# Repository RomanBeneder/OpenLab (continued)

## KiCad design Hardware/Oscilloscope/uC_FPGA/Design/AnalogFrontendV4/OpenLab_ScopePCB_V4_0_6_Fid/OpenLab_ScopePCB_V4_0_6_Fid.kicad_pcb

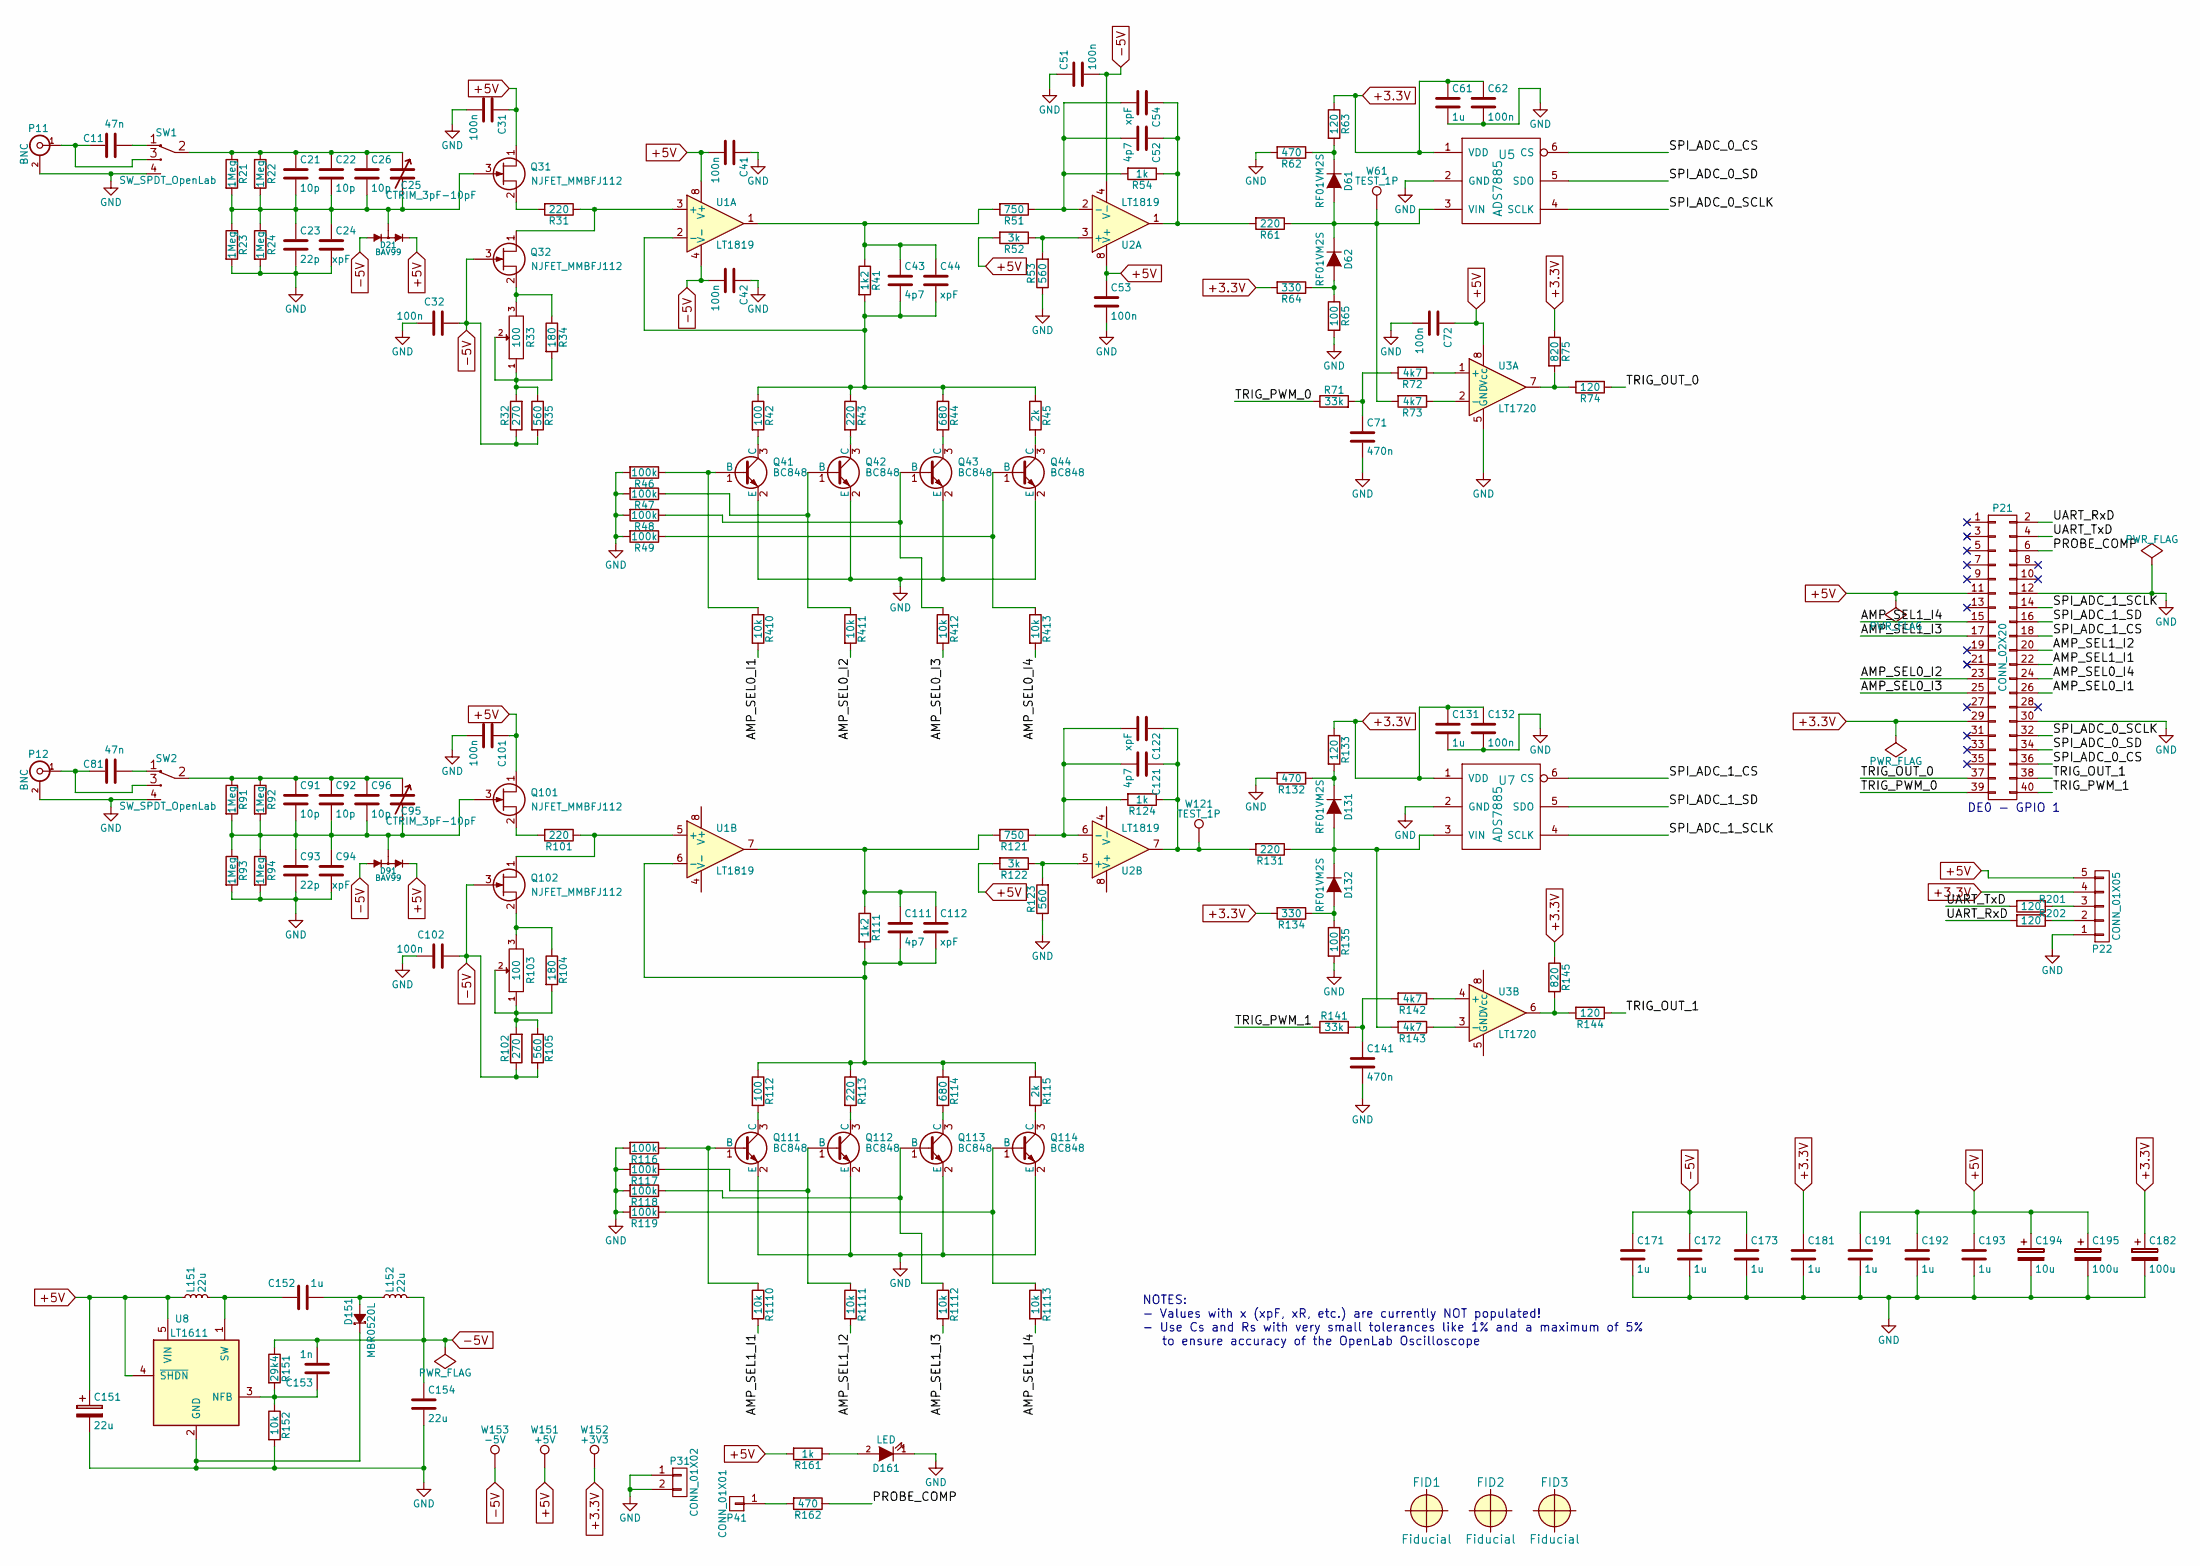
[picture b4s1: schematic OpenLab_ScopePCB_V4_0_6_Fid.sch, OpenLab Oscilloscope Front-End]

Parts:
C11, C81: 47n; C_0603_HandSoldering
C21, C22, C26, C91, C92, C96: 10p; C_0603_HandSoldering
C23, C93: 22p; C_0603_HandSoldering
C24, C44, C54, C94, C112, C122: xpF; C_0603_HandSoldering
C25, C95: CTRIM_3pF-10pF; TRIM_CO
C31, C32, C41, C42, C51, C53, C62, C72, C101, C102, C132: 100n; C_0603_HandSoldering
C43, C52, C111, C121: 4p7; C_0603_HandSoldering
C61, C131, C152, C171, C172, C173, C181, C191, C192, C193: 1u; C_0603_HandSoldering
C71, C141: 470n; C_0603_HandSoldering
C151: 22u; C_1206_HandSoldering
C153: 1n; C_0603_HandSoldering
C154: 22u; C_1210_HandSoldering
C182, C195: 100u; c_elec_6.3x5.8
C194: 10u; c_elec_5x5.3
D21, D91: BAV99; SOT-23
D61, D62, D131, D132: RF01VM2S; SOD-323_RF01VM_DIODE
D151: MBR0520L; D_SOD-123
D161: LED; LED-0805
FID1, FID2, FID3: Fiducial; Fiducial_1.5mm_Dia_2.54mm_Outer_CopperTop
L151, L152: 22u; Choke_SMD_Bourns_SRN4026
P11, P12: BNC; BNC_Socket_TYCO-AMP
P21: CONN_02X20; Pin_Header_Straight_2x20_Pitch2.54mm_OPENLAB
P22: CONN_01X05; Pin_Header_Straight_1x05_Pitch2.54mm
P31: CONN_01X02; Pin_Header_Straight_2x01_Pitch2.54mm
P41: CONN_01X01; Pin_Header_Straight_1x01_Pitch2.54mm
Q31, Q32, Q101, Q102: NJFET_MMBFJ112; SOT-23
Q41, Q42, Q43, Q44, Q111, Q112, Q113, Q114: BC848; SOT-23
R21, R22, R23, R24, R91, R92, R93, R94: 1Meg; R_0603_HandSoldering
R31, R43, R61, R101, R113, R131: 220; R_0603_HandSoldering
R32, R102: 270; R_0603_HandSoldering
R33, R103: 100; Potentiometer_SMD_OpenLab
R34, R104: 180; R_0603_HandSoldering
R35, R53, R105, R123: 560; R_0603_HandSoldering
R41, R111: 1k2; R_0603_HandSoldering
R42, R65, R112, R135: 100; R_0603_HandSoldering
R44, R114: 680; R_0603_HandSoldering
R45, R115: 2k; R_0603_HandSoldering
R46, R47, R48, R49, R116, R117, R118, R119: 100k; R_0603_HandSoldering
R51, R121: 750; R_0603_HandSoldering
R52, R122: 3k; R_0603_HandSoldering
R54, R124, R161: 1k; R_0603_HandSoldering
R62, R132, R162: 470; R_0603_HandSoldering
R63, R74, R133, R144, R201, R202: 120; R_0603_HandSoldering
R64, R134: 330; R_0603_HandSoldering
R71, R141: 33k; R_0603_HandSoldering
R72, R73, R142, R143: 4k7; R_0603_HandSoldering
R75, R145: 820; R_0603_HandSoldering
R151: 29k4; R_0603_HandSoldering
R152, R410, R411, R412, R413, R1110, R1111, R1112, R1113: 10k; R_0603_HandSoldering
SW1, SW2: SW_SPDT_OpenLab; SWITCH-2-WAY_SPDT
U1, U2: LT1819; SOIC-8_3_LT1819
U3: LT1720; SOIC-8_3_LT1819
U5, U7: ADS7885; TSOT-6_ADS7885
U8: LT1611; sot23-5_LT1611
W61, W121: TEST_1P; Test_Pad
W151: +5V; Test_Pad
W152: +3V3; Test_Pad
W153: -5V; Test_Pad

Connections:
+3.3V: C61.1, C62.1, C131.1, C132.1, C181.1, C182.1, P21.29, P22.4, R63.1, R64.2, R75.1, R133.1, R134.2, R145.1, U5.1 (VDD), U7.1 (VDD), W152.1
+5V: C31.1, C41.2, C53.1, C72.1, C101.1, C151.1, C191.1, C192.1, C193.1, C194.1, C195.1, D21.2 (K), D91.2 (K), L151.1, P21.11, P22.5, Q31.1 (D), Q101.1 (D), R52.2, R122.2, R161.2, U1.8 (V+), U2.8 (V+), U3.8 (Vcc), U8.4 (~SHDN~), U8.5 (VIN), W151.1
-5V: C32.2, C42.2, C51.2, C102.2, C153.2, C154.1, C171.1, C172.1, C173.1, D21.1 (A), D91.1 (A), L152.2, Q32.3 (G), Q102.3 (G), R32.1, R35.2, R102.1, R105.2, R151.1, U1.4 (V-), U2.4 (V-), W153.1
/AMP_SEL0_I1: P21.26, R410.2
/AMP_SEL0_I2: P21.23, R411.2
/AMP_SEL0_I3: P21.25, R412.2
/AMP_SEL0_I4: P21.24, R413.2
/AMP_SEL1_I1: P21.22, R1110.2
/AMP_SEL1_I2: P21.20, R1111.2
/AMP_SEL1_I3: P21.17, R1112.2
/AMP_SEL1_I4: P21.15, R1113.2
/PROBE_COMP: P21.6, R162.1
/SPI_ADC_0_CS: P21.36, U5.6 (CS)
/SPI_ADC_0_SCLK: P21.32, U5.4 (SCLK)
/SPI_ADC_0_SD: P21.34, U5.5 (SDO)
/SPI_ADC_1_CS: P21.18, U7.6 (CS)
/SPI_ADC_1_SCLK: P21.14, U7.4 (SCLK)
/SPI_ADC_1_SD: P21.16, U7.5 (SDO)
/TRIG_OUT_0: P21.37, R74.1
/TRIG_OUT_1: P21.38, R144.1
/TRIG_PWM_0: P21.39, R71.1
/TRIG_PWM_1: P21.40, R141.1
/UART_RxD: P21.2, R202.2
/UART_TxD: P21.4, R201.2
GND: C23.2, C24.2, C31.2, C32.1, C41.1, C42.1, C51.1, C53.2, C61.2, C62.2, C71.2, C72.2, C93.2, C94.2, C101.2, C102.1, C131.2, C132.2, C141.2, C151.2, C154.2, C171.2, C172.2, C173.2, C181.2, C182.2, C191.2, C192.2, C193.2, C194.2, C195.2, D151.1 (K), D161.1 (K), P11.2 (Ext), P12.2 (Ext), P21.12, P21.30, P22.1, P31.1, P31.2, Q41.2 (E), Q42.2 (E), Q43.2 (E), Q44.2 (E), Q111.2 (E), Q112.2 (E), Q113.2 (E), Q114.2 (E), R23.2, R24.2, R46.2, R47.2, R48.2, R49.2, R53.1, R62.2, R65.2, R93.2, R94.2, R116.2, R117.2, R118.2, R119.2, R123.1, R132.2, R135.2, R152.2, SW1.4 (FRAME), SW2.4 (FRAME), U3.5 (GND), U5.2 (GND), U7.2 (GND), U8.2 (GND)
unnamed: C11.1, SW1.1 (AC)
unnamed: C11.2, P11.1 (In), SW1.3 (DC)
unnamed: C21.1, C22.1, C25.1, C26.1, R21.1, R22.1, SW1.2 (SIG)
unnamed: C21.2, C22.2, C23.1, C24.1, C25.2, C26.2, D21.3 (KA), Q31.3 (G), R21.2, R22.2, R23.1, R24.1
unnamed: C43.1, C44.1, R41.1, R51.2, U1.1
unnamed: C43.2, C44.2, R41.2, R42.1, R43.1, R44.1, R45.1, U1.2 (-)
unnamed: C52.1, C54.1, R54.1, R61.2, U2.1
unnamed: C52.2, C54.2, R51.1, R54.2, U2.2 (-)
unnamed: C71.1, R71.2, R72.2
unnamed: C81.1, SW2.1 (AC)
unnamed: C81.2, P12.1 (In), SW2.3 (DC)
unnamed: C91.1, C92.1, C95.1, C96.1, R91.1, R92.1, SW2.2 (SIG)
unnamed: C91.2, C92.2, C93.1, C94.1, C95.2, C96.2, D91.3 (KA), Q101.3 (G), R91.2, R92.2, R93.1, R94.1
unnamed: C111.1, C112.1, R111.1, R121.2, U1.7
unnamed: C111.2, C112.2, R111.2, R112.1, R113.1, R114.1, R115.1, U1.6 (-)
unnamed: C121.1, C122.1, R124.1, R131.2, U2.7, W121.1
unnamed: C121.2, C122.2, R121.1, R124.2, U2.6 (-)
unnamed: C141.1, R141.2, R142.2
unnamed: C152.1, L151.2, U8.1 (SW)
unnamed: C152.2, D151.2 (A), L152.1
unnamed: C153.1, R151.2, R152.1, U8.3 (NFB)
unnamed: D61.1 (K), R62.1, R63.2
unnamed: D61.2 (A), D62.1 (K), R61.1, R73.2, U5.3 (VIN), W61.1
unnamed: D62.2 (A), R64.1, R65.1
unnamed: D131.1 (K), R132.1, R133.2
unnamed: D131.2 (A), D132.1 (K), R131.1, R143.2, U7.3 (VIN)
unnamed: D132.2 (A), R134.1, R135.1
unnamed: D161.2 (A), R161.1
unnamed: P22.2, R202.1
unnamed: P22.3, R201.1
unnamed: P41.1, R162.2
unnamed: Q31.2 (S), R31.2
unnamed: Q32.1 (D), R31.1, U1.3 (+)
unnamed: Q32.2 (S), R33.3, R34.1
unnamed: Q41.1 (B), R46.1, R410.1
unnamed: Q41.3 (C), R42.2
unnamed: Q42.1 (B), R47.1, R411.1
unnamed: Q42.3 (C), R43.2
unnamed: Q43.1 (B), R48.1, R412.1
unnamed: Q43.3 (C), R44.2
unnamed: Q44.1 (B), R49.1, R413.1
unnamed: Q44.3 (C), R45.2
unnamed: Q101.2 (S), R101.2
unnamed: Q102.1 (D), R101.1, U1.5 (+)
unnamed: Q102.2 (S), R103.3, R104.1
unnamed: Q111.1 (B), R116.1, R1110.1
unnamed: Q111.3 (C), R112.2
unnamed: Q112.1 (B), R117.1, R1111.1
unnamed: Q112.3 (C), R113.2
unnamed: Q113.1 (B), R118.1, R1112.1
unnamed: Q113.3 (C), R114.2
unnamed: Q114.1 (B), R119.1, R1113.1
unnamed: Q114.3 (C), R115.2
unnamed: R32.2, R33.1, R33.2, R34.2, R35.1
unnamed: R52.1, R53.2, U2.3 (+)
unnamed: R72.1, U3.1 (+)
unnamed: R73.1, U3.2 (-)
unnamed: R74.2, R75.2, U3.7
unnamed: R102.2, R103.1, R103.2, R104.2, R105.1
unnamed: R122.1, R123.2, U2.5 (+)
unnamed: R142.1, U3.4 (+)
unnamed: R143.1, U3.3 (-)
unnamed: R144.2, R145.2, U3.6

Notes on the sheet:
DE0 - GPIO 1
NOTES: - Values with x (xpF, xR, etc.) are currently NOT populated! - Use Cs and Rs with very small tolerances like 1% and a maximum of 5% to ensure accuracy of the OpenLab Oscilloscope

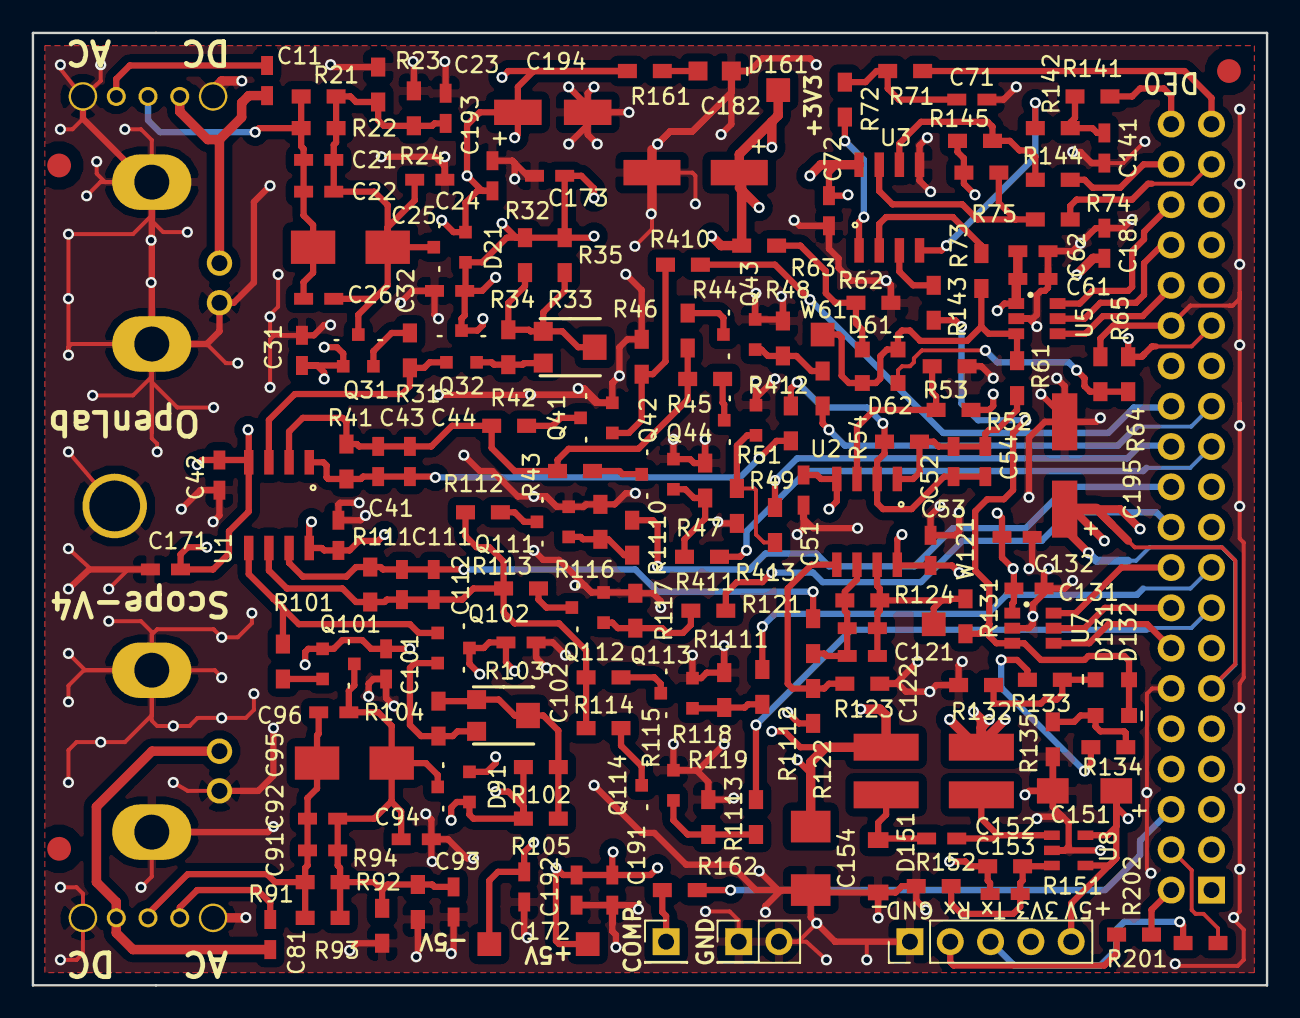
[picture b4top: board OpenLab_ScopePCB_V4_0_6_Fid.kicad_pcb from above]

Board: 4 copper layers, 77.8 x 60.0 mm, 173 parts (0 on the bottom side), 88 nets.

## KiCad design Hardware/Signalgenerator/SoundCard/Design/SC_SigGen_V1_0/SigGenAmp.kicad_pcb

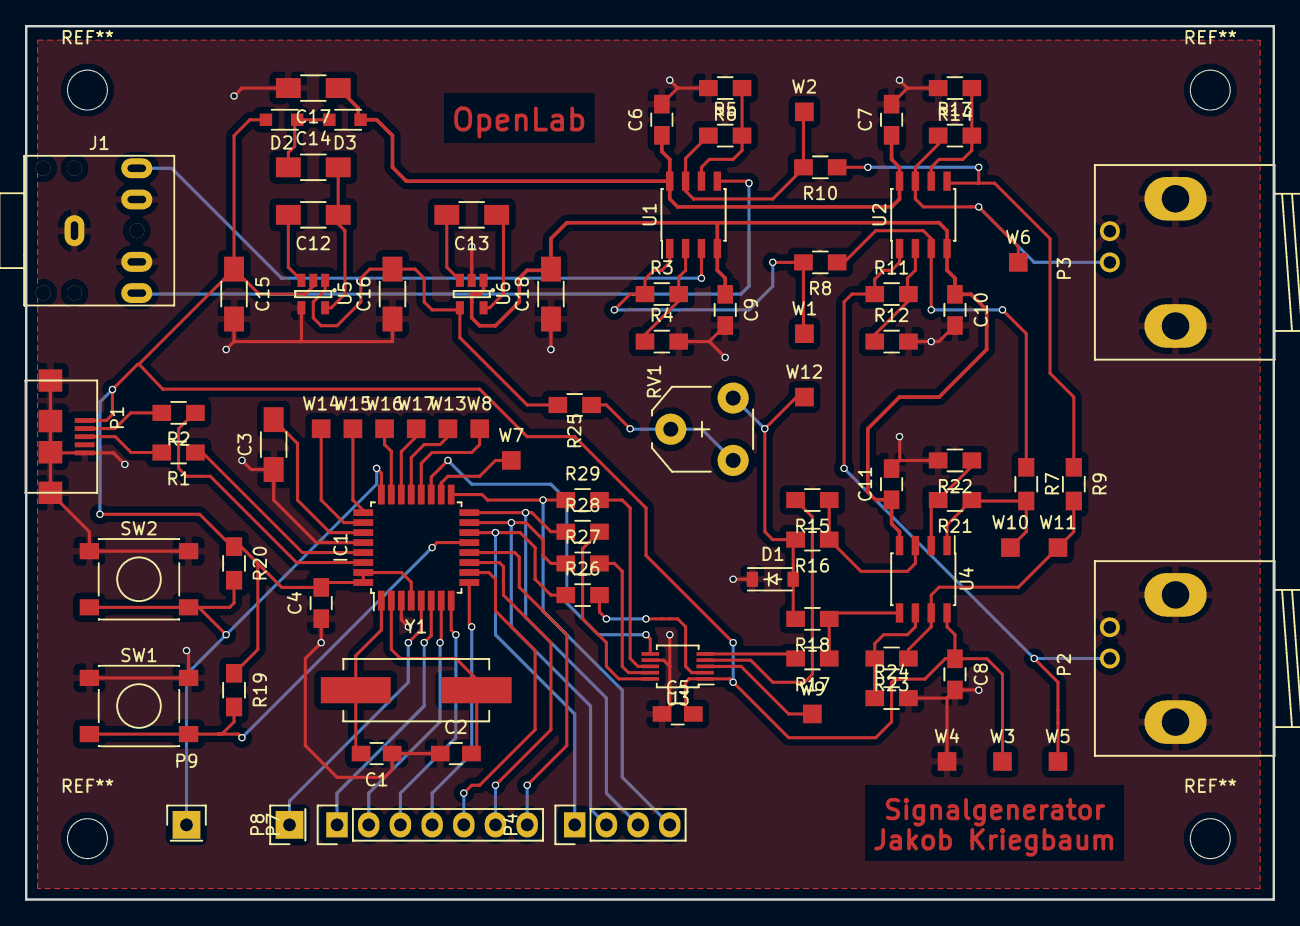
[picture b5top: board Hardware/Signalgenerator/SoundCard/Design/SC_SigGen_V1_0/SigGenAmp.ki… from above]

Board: 2 copper layers, 100.0 x 70.0 mm, 86 parts (0 on the bottom side), 66 nets.

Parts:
C1, C2: 22pF; C_0805_HandSoldering
C3, C12, C13, C14, C15, C16, C17, C18: 1uF; C_1206_HandSoldering
C4: 100nF; C_0805_HandSoldering
C5, C6, C7, C8, C9, C10, C11: 100n; C_0805_HandSoldering
D1: 2.5V; SOD-123
D2, D3: D; SOD-323_HandSoldering
IC1: ATMEGA8U2; TQFP-32_7x7mm_Pitch0.8mm
J1: JACK_TRS_6PINS; TRS 3.5mm 5PIN
P1: USB_OTG; USB_Micro-B_SMD
P2: CH1; BNC_Socket_TYCO-AMP_FIX
P3: CH2; BNC_Socket_TYCO-AMP_FIX
P4: SPI; Pin_Header_Straight_1x04
P7: PORTD; Pin_Header_Straight_1x07
P8: PC; Pin_Header_Straight_1x01
P9: dW; Pin_Header_Straight_1x01
R1, R2: 22; R_0805_HandSoldering
R3, R5: 110k; R_0805_HandSoldering
R4, R6, R11, R12, R13, R14, R19, R20, R22, R24: 10k; R_0805_HandSoldering
R7, R8, R9, R10, R15, R16, R17, R18: 100k; R_0805_HandSoldering
R21, R23: 30k; R_0805_HandSoldering
R25: 1k; R_0805_HandSoldering
R26, R27, R28, R29: 100; R_0805_HandSoldering
RV1: 2k5; Potentiometer_VishaySpectrol-Econtrim-Type36M
SW1, SW2: SW_PUSH; SW_SPST_PTS645
U1, U2: AD8034; SOIC-8_3.9x4.9mm_Pitch1.27mm
U3: MCP48FEB02; MSOP-10_3x3mm_Pitch0.5mm
U4: MC33202; SOIC-8_3.9x4.9mm_Pitch1.27mm
U5, U6: TPS60400DBVR; SOT-23-5
W1: AMP1; Measurement_Point_Square-SMD-Pad_Small
W2: AMP2; Measurement_Point_Square-SMD-Pad_Small
W3: VCC; Measurement_Point_Square-SMD-Pad_Small
W4: GND; Measurement_Point_Square-SMD-Pad_Small
W5: SIG1; Measurement_Point_Square-SMD-Pad_Small
W6: SIG2; Measurement_Point_Square-SMD-Pad_Small
W7: PB4; Measurement_Point_Square-SMD-Pad_Small
W8: PB6; Measurement_Point_Square-SMD-Pad_Small
W9: DACREF; Measurement_Point_Square-SMD-Pad_Small
W10: OFF1; Measurement_Point_Square-SMD-Pad_Small
W11: OFF2; Measurement_Point_Square-SMD-Pad_Small
W12: REF; Measurement_Point_Square-SMD-Pad_Small
W13, W14, W15, W16, W17: PB7; Measurement_Point_Square-SMD-Pad_Small
Y1: 16MHz; Crystal_HC49-SD_SMD

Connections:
GND: C1.1, C2.1, C3.1, C4.1, C5.1, C6.2, C7.2, C8.2, C9.2, C10.2, C11.2, C15.2, C16.1, C17.2, C18.1, D1.1, IC1.3, IC1.28, J1.1, J1.5, J1.6, P1.5, P1.6, P2.2, P3.2, R4.2, R6.2, R12.2, R14.2, R22.2, R24.2, SW1.1, SW2.1, U3.7, U5.4, U6.2, W4.1
HWB: IC1.13, R19.2, SW1.2
unnamed: C1.2, IC1.1, Y1.1
unnamed: C2.2, IC1.2, Y1.2
unnamed: C3.2, IC1.27
unnamed: C12.1, C14.2, U5.5
unnamed: C12.2, U5.3
unnamed: C13.1, U6.5
unnamed: C13.2, U6.3
unnamed: C14.1, D2.1, D3.2
unnamed: IC1.5, P8.1
unnamed: IC1.6, P7.1
unnamed: IC1.7, P7.2
unnamed: IC1.8, P7.3
unnamed: IC1.9, P7.4
unnamed: IC1.10, P7.5
unnamed: IC1.11, P7.6
unnamed: IC1.12, P7.7
unnamed: IC1.14, P4.1, R26.1
unnamed: IC1.15, P4.2, R27.1
unnamed: IC1.16, P4.3, R28.1
unnamed: IC1.17, P4.4, R29.1
unnamed: IC1.18, W7.1
unnamed: IC1.19, U3.6
unnamed: IC1.20, W8.1
unnamed: IC1.21, W13.1
unnamed: IC1.22, W17.1
unnamed: IC1.23, W16.1
unnamed: IC1.25, W15.1
unnamed: IC1.26, W14.1
unnamed: IC1.29, R1.1
unnamed: IC1.30, R2.1
unnamed: J1.2, U1.3
unnamed: J1.3, U1.5
unnamed: P1.2, R2.2
unnamed: P1.3, R1.2
unnamed: P2.1, R11.1, U2.1, W5.1
unnamed: P3.1, R13.1, U2.7, W6.1
unnamed: R3.1, R8.2, U1.1, W1.1
unnamed: R3.2, R4.1, U1.2
unnamed: R5.2, R6.1, U1.6
unnamed: R7.1, R8.1, U2.3
unnamed: R9.1, R10.1, U2.5
unnamed: R5.1, R10.2, U1.7, W2.1
unnamed: R11.2, R12.1, U2.2
unnamed: R13.2, R14.1, U2.6
unnamed: R15.1, R16.1, U4.3
unnamed: R17.1, R18.1, U4.5
unnamed: R21.2, R22.1, U4.2
unnamed: R23.2, R24.1, U4.6
unnamed: R25.1, RV1.1, RV1.2
unnamed: R26.2, U3.2
unnamed: R27.2, U3.9
unnamed: R28.2, U3.10
unnamed: R29.2, U3.8
unnamed: U3.3, W9.1
Offset1: R7.2, R21.1, U4.1, W10.1
Offset2: R9.2, R23.1, U4.7, W11.1
RESET: IC1.24, P9.1, R20.2, SW2.2
RawOffset1: R15.2, U3.4
RawOffset2: R17.2, U3.5
V+: C6.1, C7.1, C17.1, D3.1, U1.8, U2.8
V-: C9.1, C10.1, C11.1, C18.2, U1.4, U2.4, U4.4, U6.1
VCC: C4.2, C5.2, C8.1, C15.1, D2.2, IC1.4, IC1.31, IC1.32, P1.1, R19.1, R20.1, U3.1, U4.8, U5.2, W3.1
VRef-: D1.2, R16.2, R18.2, RV1.3, W12.1
VSS: C16.2, R25.2, U5.1, U6.4

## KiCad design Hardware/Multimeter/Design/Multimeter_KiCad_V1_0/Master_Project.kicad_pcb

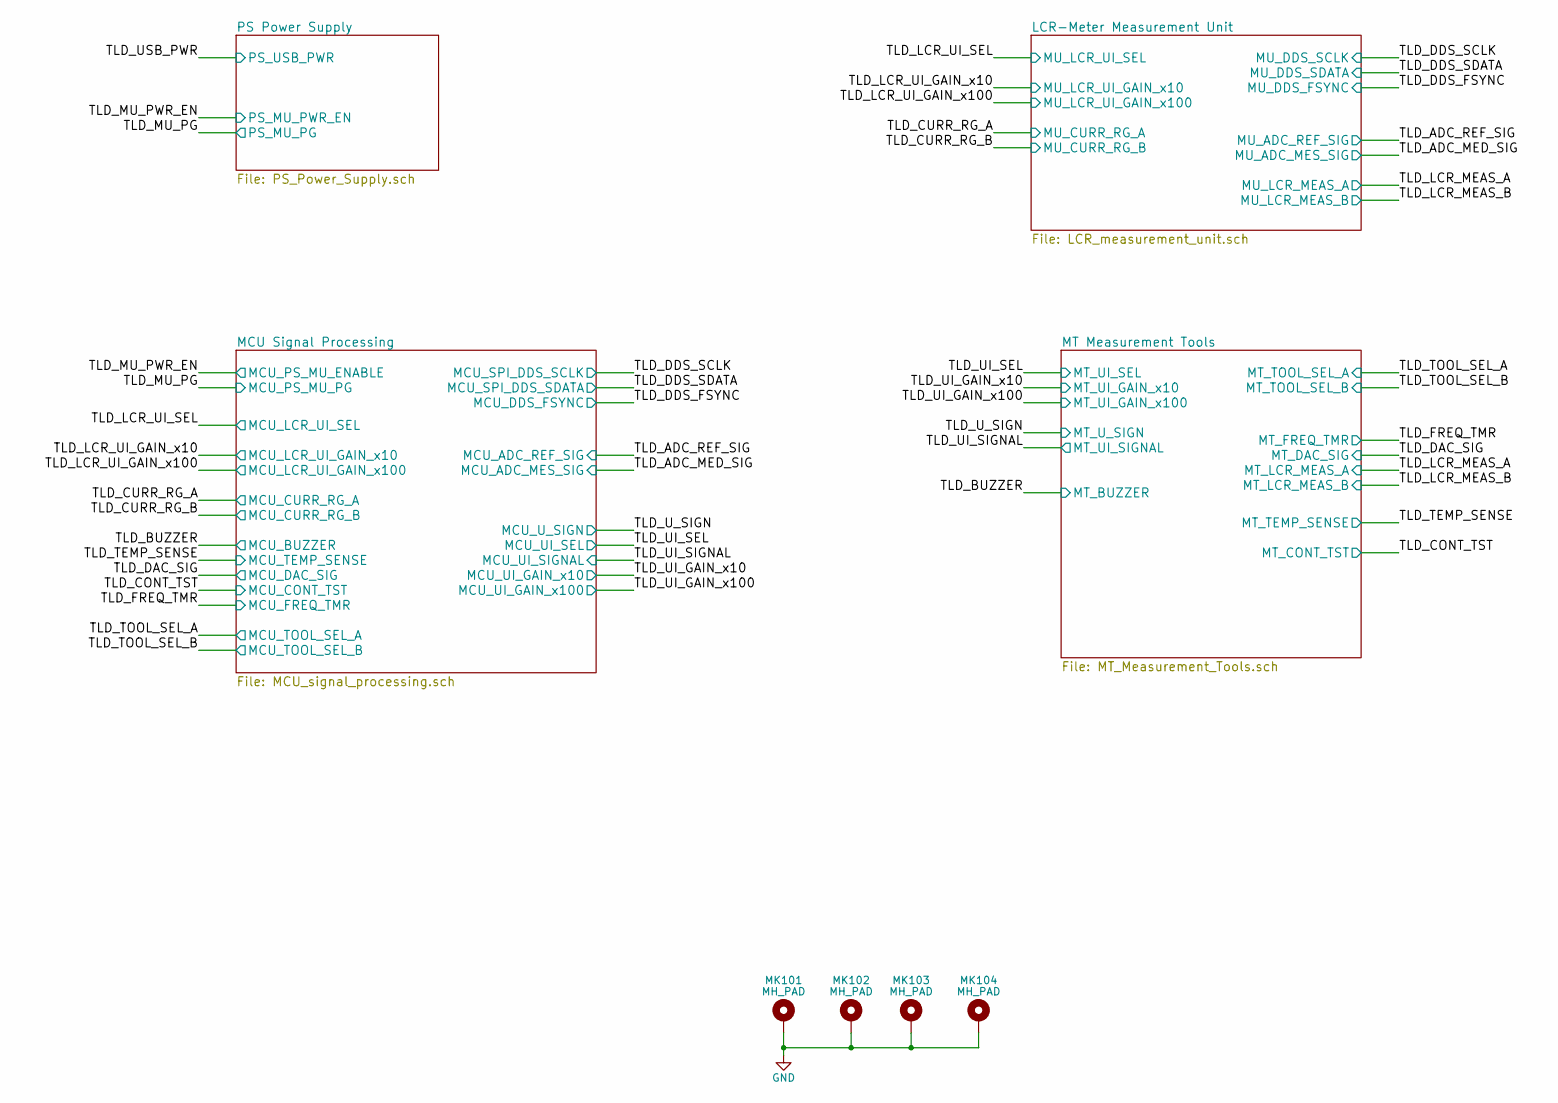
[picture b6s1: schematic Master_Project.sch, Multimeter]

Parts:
MK101, MK102, MK103, MK104: MH_PAD; MountingHole_3.2mm_M3_DIN965_Pad

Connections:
GND: MK101.1, MK102.1, MK103.1, MK104.1; also elsewhere on the board

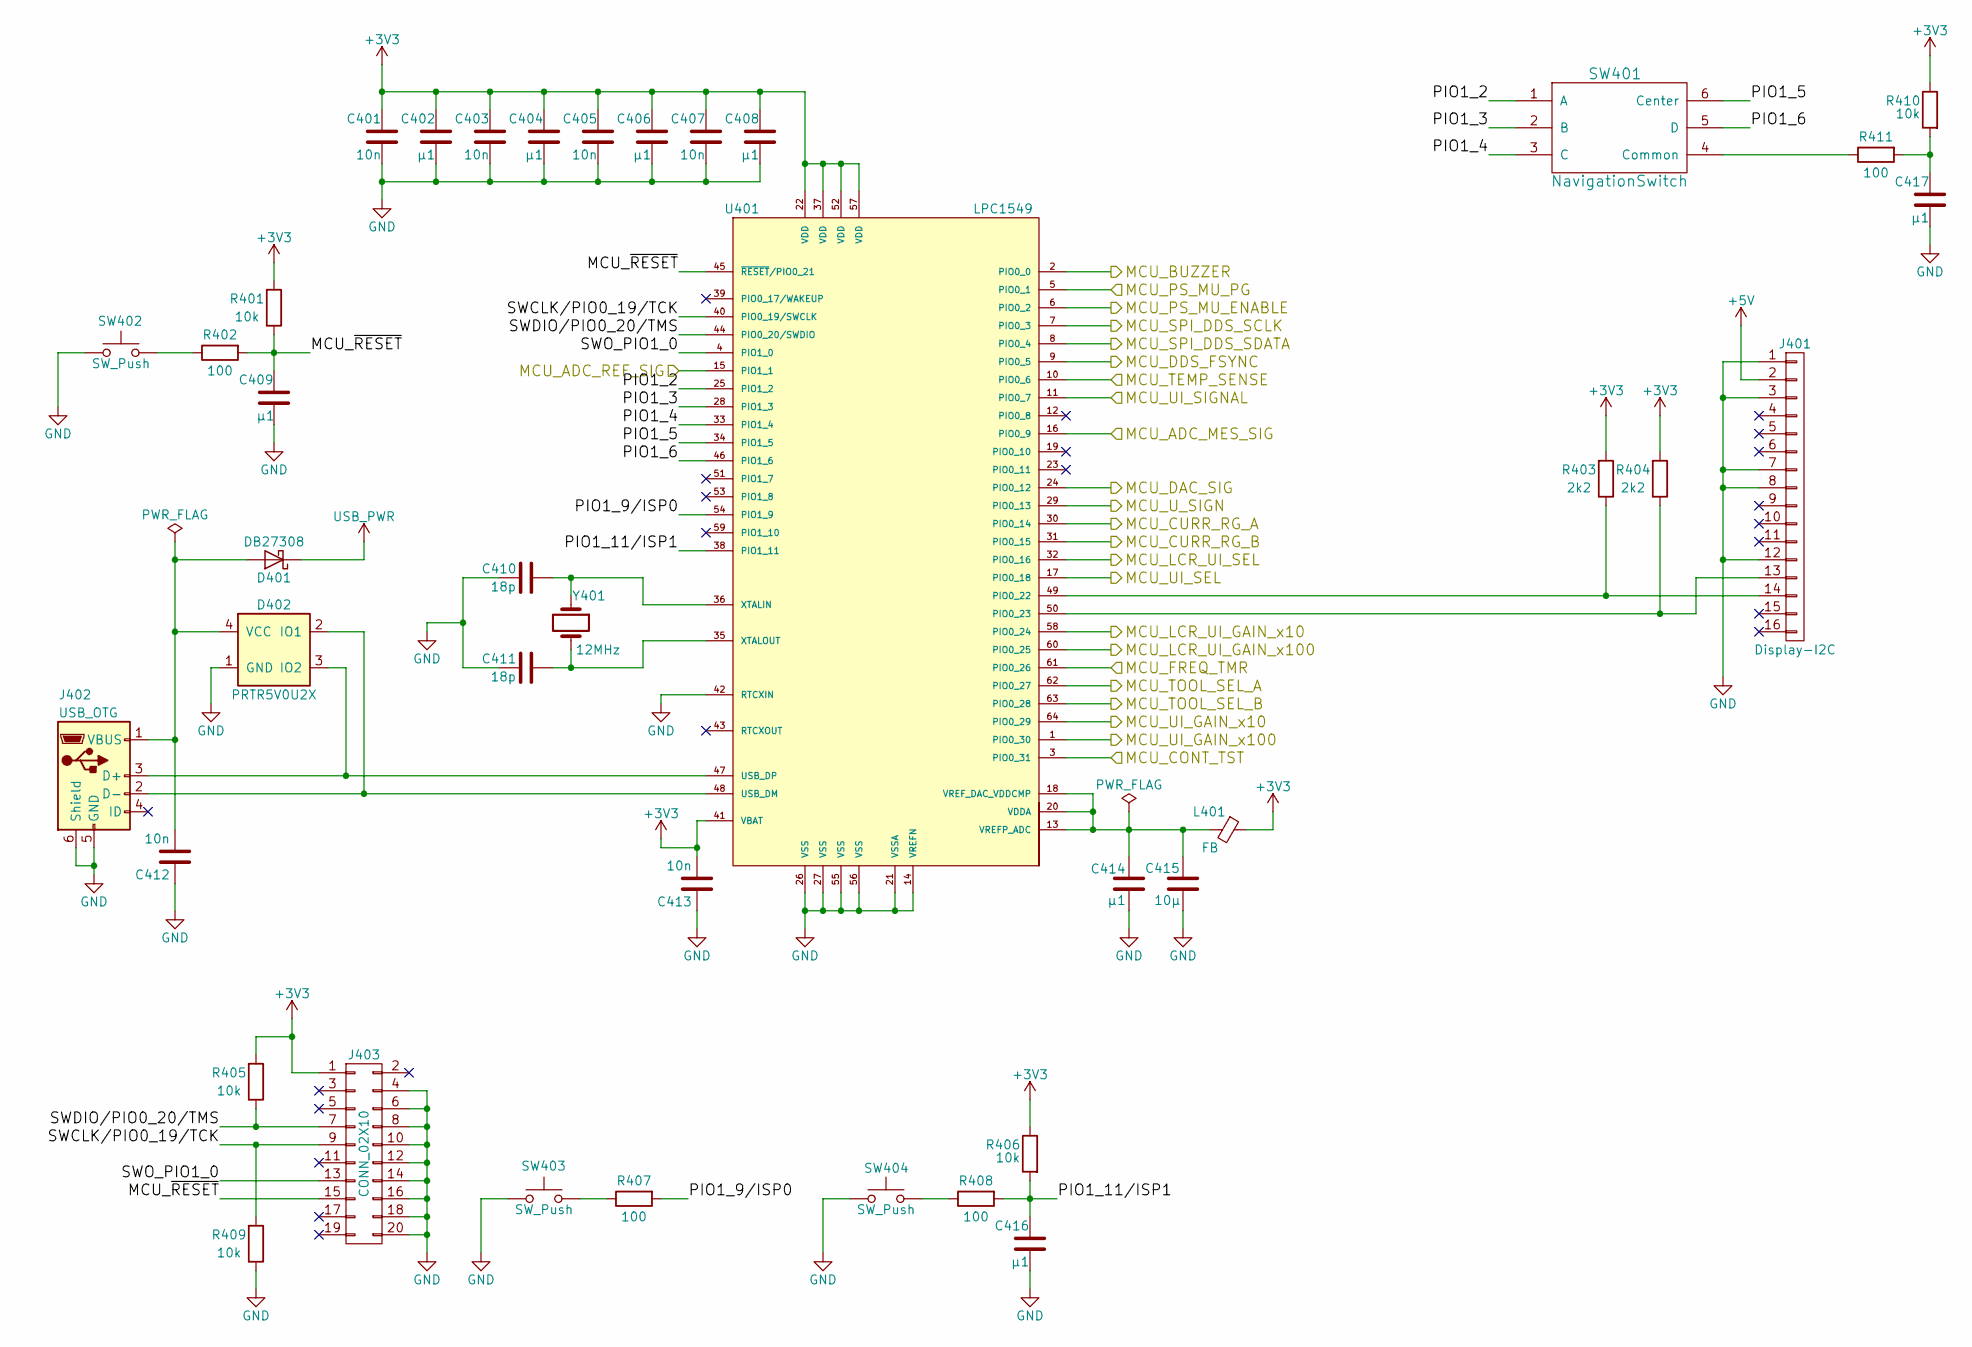
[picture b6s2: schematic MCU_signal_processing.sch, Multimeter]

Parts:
C401, C403, C405, C407, C412, C413: 10n; C_0603
C402, C404, C406, C408, C409, C414, C416, C417: µ1; C_0603
C410, C411: 18p; C_0603
C415: 10µ; C_1206
D401: DB27308; D_0603
D402: PRTR5V0U2X; SOT-143
J401: Display-I2C; Pin_Header_Straight_1x16_Pitch2.54mm
J402: USB_OTG; USB_Micro_B
J403: CONN_02X10; Pin_Header_Straight_2x10_Pitch2.54mm
L401: FB; R_0805
R401, R405, R406, R409, R410: 10k; R_0603
R402, R407, R408, R411: 100; R_0603
R403, R404: 2k2; R_0603
SW401: NavigationSwitch; SKQUCAA010_SKQU_5_Polig_ALPS
SW402, SW403, SW404: SW_Push; SW_SPST_KMR2
U401: LPC1549; LQFP-64_10x10mm_Pitch0.5mm
Y401: 12MHz; Crystal_SMD_0603-2pin_6.0x3.5mm

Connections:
+3V3: C401.2, C402.2, C403.2, C404.2, C405.2, C406.2, C407.2, C408.2, C413.2, J403.1, L401.1, R401.2, R403.2, R404.2, R405.2, R406.1, R410.1, U401.22 (VDD), U401.37 (VDD), U401.41 (VBAT), U401.52 (VDD), U401.57 (VDD); also elsewhere on the board
+5V: J401.2; also elsewhere on the board
/MCU Signal Processing/MCU_~RESET~: C409.2, J403.15, R401.1, R402.2, U401.45 (~RESET~/PIO0_21)
/MCU Signal Processing/PIO1_2: SW401.1 (A), U401.25 (PIO1_2)
/MCU Signal Processing/PIO1_3: SW401.2 (B), U401.28 (PIO1_3)
/MCU Signal Processing/PIO1_4: SW401.3 (C), U401.33 (PIO1_4)
/MCU Signal Processing/PIO1_5: SW401.6 (Center), U401.34 (PIO1_5)
/MCU Signal Processing/PIO1_6: SW401.5 (D), U401.46 (PIO1_6)
/MCU Signal Processing/PIO1_9/ISP0: R407.2, U401.54 (PIO1_9)
/MCU Signal Processing/PIO1_11/ISP1: C416.2, R406.2, R408.2, U401.38 (PIO1_11)
/MCU Signal Processing/SWCLK/PIO0_19/TCK: J403.9, R409.2, U401.40 (PIO0_19/SWCLK)
/MCU Signal Processing/SWDIO/PIO0_20/TMS: J403.7, R405.1, U401.44 (PIO0_20/SWDIO)
/MCU Signal Processing/SWO_PIO1_0: J403.13, U401.4 (PIO1_0)
/TLD_ADC_MED_SIG: U401.16 (PIO0_9); also elsewhere on the board
/TLD_ADC_REF_SIG: U401.15 (PIO1_1); also elsewhere on the board
/TLD_BUZZER: U401.2 (PIO0_0); also elsewhere on the board
/TLD_CONT_TST: U401.3 (PIO0_31); also elsewhere on the board
/TLD_CURR_RG_A: U401.30 (PIO0_14); also elsewhere on the board
/TLD_CURR_RG_B: U401.31 (PIO0_15); also elsewhere on the board
/TLD_DAC_SIG: U401.24 (PIO0_12); also elsewhere on the board
/TLD_DDS_FSYNC: U401.9 (PIO0_5); also elsewhere on the board
/TLD_DDS_SCLK: U401.7 (PIO0_3); also elsewhere on the board
/TLD_DDS_SDATA: U401.8 (PIO0_4); also elsewhere on the board
/TLD_FREQ_TMR: U401.61 (PIO0_26); also elsewhere on the board
/TLD_LCR_UI_GAIN_x10: U401.58 (PIO0_24); also elsewhere on the board
/TLD_LCR_UI_GAIN_x100: U401.60 (PIO0_25); also elsewhere on the board
/TLD_LCR_UI_SEL: U401.32 (PIO0_16); also elsewhere on the board
/TLD_MU_PG: U401.5 (PIO0_1); also elsewhere on the board
/TLD_MU_PWR_EN: U401.6 (PIO0_2); also elsewhere on the board
/TLD_TEMP_SENSE: U401.10 (PIO0_6); also elsewhere on the board
/TLD_TOOL_SEL_A: U401.62 (PIO0_27); also elsewhere on the board
/TLD_TOOL_SEL_B: U401.63 (PIO0_28); also elsewhere on the board
/TLD_UI_GAIN_x10: U401.64 (PIO0_29); also elsewhere on the board
/TLD_UI_GAIN_x100: U401.1 (PIO0_30); also elsewhere on the board
/TLD_UI_SEL: U401.17 (PIO0_18); also elsewhere on the board
/TLD_UI_SIGNAL: U401.11 (PIO0_7); also elsewhere on the board
/TLD_U_SIGN: U401.29 (PIO0_13); also elsewhere on the board
GND: C401.1, C402.1, C403.1, C404.1, C405.1, C406.1, C407.1, C408.1, C409.1, C410.2, C411.2, C412.1, C413.1, C414.1, C415.1, C416.1, C417.1, D402.1 (GND), J401.1, J401.3, J401.7, J401.8, J401.12, J402.5 (GND), J402.6 (Shield), J403.4, J403.6, J403.8, J403.10, J403.12, J403.14, J403.16, J403.18, J403.20, R409.1, SW402.1, SW403.1, SW404.1, U401.14 (VREFN), U401.21 (VSSA), U401.26 (VSS), U401.27 (VSS), U401.42 (RTCXIN), U401.55 (VSS), U401.56 (VSS); also elsewhere on the board
unnamed: C410.1, U401.36 (XTALIN), Y401.1
unnamed: C411.1, U401.35 (XTALOUT), Y401.2
unnamed: C412.2, D401.2 (A), D402.4 (VCC), J402.1 (VBUS)
unnamed: C414.2, C415.2, L401.2, U401.13 (VREFP_ADC), U401.18 (VREF_DAC_VDDCMP), U401.20 (VDDA)
unnamed: C417.2, R410.2, R411.2
unnamed: D402.2 (IO1), J402.2 (D-), U401.48 (USB_DM)
unnamed: D402.3 (IO2), J402.3 (D+), U401.47 (USB_DP)
unnamed: J401.13, R404.1, U401.50 (PIO0_23)
unnamed: J401.14, R403.1, U401.49 (PIO0_22)
unnamed: R402.1, SW402.2
unnamed: R407.1, SW403.2
unnamed: R408.1, SW404.2
unnamed: R411.1, SW401.4 (Common)
USB_PWR: D401.1 (K); also elsewhere on the board
